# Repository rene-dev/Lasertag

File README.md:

# Lasertag
pew pew!
Ein freies und offenes Lasertag Projekt der warpzone in Münster.

## Aktueller Stand
Hard- und Software haben viele Kinderkrankheiten, spielbar ist es noch nicht. Es existieren 2 Waffel-Prototypen mit tiefgezogenen Gehäusen und ein Paar Hitpoints. Westen wollen noch gebaut werden.
* __Hitpoint__: voll funktionsfähig aber dirty gecoded
* __Lasermodul__: Im groben funktioniert alles. Einige Pins sind falsch beschriftet. IR funktioniert, sendet auch ganz leicht wenn es nicht senden soll. Sound ist viel zu leise.
* __Pi__: Da ist noch einiges zu tun. Grundlegende Kommunikation mit den Modulen ist möglich. Grundlegender Server Client per TCP.

## Grundstruktur
In jeder Waffel steckt ein Raspberry Pi, ein Lasermodul und ein Hitpoint. Das Lasermodul ist ein HAT für den Pi und dient als Schnittstelle zur Waffel-Hardware. Die High-Level Kommunikation (Spielmodus, Powerups, Map, ...) zwischen den Pis läuft per WLAN. Die Low-Level Kommunikation (Player-ID, Schaden) per gebündeltem IR-LED-UART auf TSOP-Empfänger.

### Raspberry Pi
In Python wird Netzwerk gemacht, per I2C die Module angesprochen und das SPI-Touch-Display angesteuert.

### Lasermodul
Kommt in jede Waffel:
* Atmega 328p
* IR-LED zum Daten senden
* roten Laser, damit man auch was sieht (Klasse 1 mit deutschem Zertifikat)
* starke RGBW ansteuern für Lichteffekte
* Trefferzone über einen Front-TSOP
* Taster auslesen
* LiPo auf 5V Step-Up Wandler
* An-Aus Taster
* Akkuüberwachung
* Audioverstärker

### Hitpoint
Kommt in jede Waffel und mehrere an die Weste (Schultern, Bauch, Rücken, ...):
* Attiny 2313A
* 4 10mm RGB-LEDs
* 4 TSOP-IR-Empfänger

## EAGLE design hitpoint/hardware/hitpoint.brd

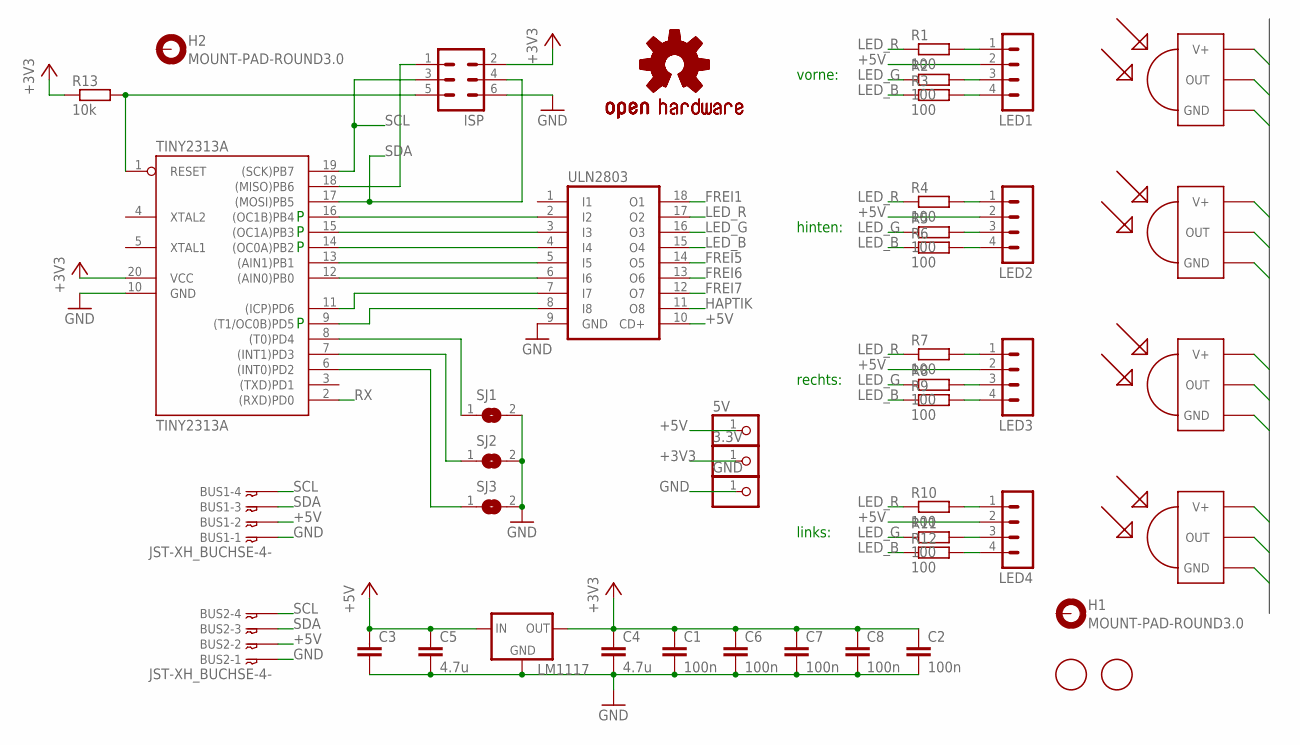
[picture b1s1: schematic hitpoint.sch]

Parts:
3.3V, 5V: PIN-HEADER-1
BUS1, BUS2: JST-XH_BUCHSE-4-; JST-XH_BUCHSE-4
C1, C2, C6, C7, C8: 100n; 0603
C3: C_EUCAP_UNIVERSAL; C_UNIVERSAL
C4, C5: 4.7u; 0805
GND: PIN-HEADER-1
H1, H2: MOUNT-PAD-ROUND3.0; 3,0-PAD
ISP: PIN-HEADER-3X2
LED1, LED2, LED3, LED4: PIN-HEADER-4
LM1117: LM1117_3V3_REGULATOR; SOT223
LOGO1, LOGO2: OSHW-LOGOM; OSHW-LOGO-M
R1, R2, R3, R4, R5, R6, R7, R8, R9, R10, R11, R12: 100; 0603
R13: 10k; 0603
SJ1, SJ2, SJ3: SJ
TINY2313A: TINY2313A; SO20LVERSTUMMELT
U$1, U$2, U$3, U$4: TSOP4338
U$5, U$6: FIDUCIAL; FIDUCIAL_1MM
ULN2803: ULN2803ASO18; SO18W

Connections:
+3V3: 3.3V.1, C1.1, C2.1, C4.1, C6.1, C7.1, C8.1, ISP.2, LM1117.2 (OUT), LM1117.4 (OUT), R13.1, TINY2313A.20 (VCC), U$1.VCC (V+), U$2.VCC (V+), U$3.VCC (V+), U$4.VCC (V+)
+5V: 5V.1, BUS1.P$2, BUS2.P$2, C3.1, C3.1B (1), C5.1, LED1.2, LED2.2, LED3.2, LED4.2, LM1117.3 (IN), ULN2803.10 (CD+)
FREI1: ULN2803.18 (O1)
FREI5: ULN2803.14 (O5)
FREI6: ULN2803.13 (O6)
FREI7: ULN2803.12 (O7)
GND: BUS1.P$1, BUS2.P$1, C1.2, C2.2, C3.2, C3.2B (2), C4.2, C5.2, C6.2, C7.2, C8.2, GND.1, ISP.6, LM1117.1 (GND), SJ1.2, SJ2.2, SJ3.2, TINY2313A.10 (GND), U$1.GND, U$2.GND, U$3.GND, U$4.GND, ULN2803.9 (GND)
HAPTIK: ULN2803.11 (O8)
LED_B: R3.1, R6.1, R9.1, R12.1, ULN2803.15 (O4)
LED_G: R2.1, R5.1, R8.1, R11.1, ULN2803.16 (O3)
LED_R: R1.1, R4.1, R7.1, R10.1, ULN2803.17 (O2)
unnamed: ISP.1, TINY2313A.18 ((MISO)PB6)
unnamed: SJ1.1, TINY2313A.8 ((T0)PD4)
unnamed: TINY2313A.16 ((OC1B)PB4), ULN2803.2 (I2)
unnamed: TINY2313A.15 ((OC1A)PB3), ULN2803.3 (I3)
unnamed: LED4.1, R10.2
unnamed: LED4.3, R11.2
unnamed: TINY2313A.14 ((OC0A)PB2), ULN2803.4 (I4)
unnamed: TINY2313A.13 ((AIN1)PB1), ULN2803.5 (I5)
unnamed: TINY2313A.12 ((AIN0)PB0), ULN2803.6 (I6)
unnamed: TINY2313A.11 ((ICP)PD6), ULN2803.7 (I7)
unnamed: TINY2313A.9 ((T1/OC0B)PD5), ULN2803.8 (I8)
unnamed: LED4.4, R12.2
unnamed: LED3.1, R7.2
unnamed: LED3.3, R8.2
unnamed: LED3.4, R9.2
unnamed: LED2.1, R4.2
unnamed: LED2.3, R5.2
unnamed: SJ2.1, TINY2313A.7 ((INT1)PD3)
unnamed: SJ3.1, TINY2313A.6 ((INT0)PD2)
unnamed: LED2.4, R6.2
unnamed: ISP.5, R13.2, TINY2313A.1 (RESET)
unnamed: LED1.1, R1.2
unnamed: LED1.3, R2.2
unnamed: LED1.4, R3.2
RX: TINY2313A.2 ((RXD)PD0), U$1.OUT, U$2.OUT, U$3.OUT, U$4.OUT
SCL: BUS1.P$4, BUS2.P$4, ISP.3, TINY2313A.19 ((SCK)PB7)
SDA: BUS1.P$3, BUS2.P$3, ISP.4, TINY2313A.17 ((MOSI)PB5)

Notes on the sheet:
vorne:
hinten:
rechts:
links:

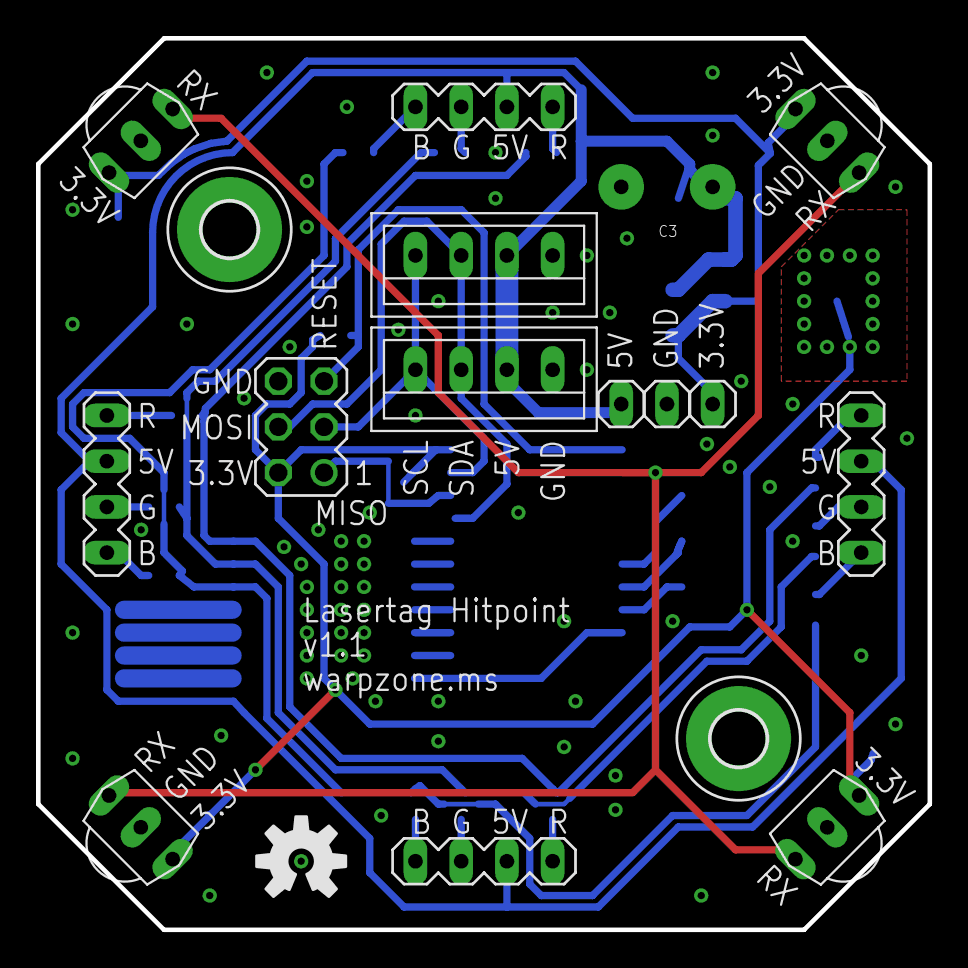
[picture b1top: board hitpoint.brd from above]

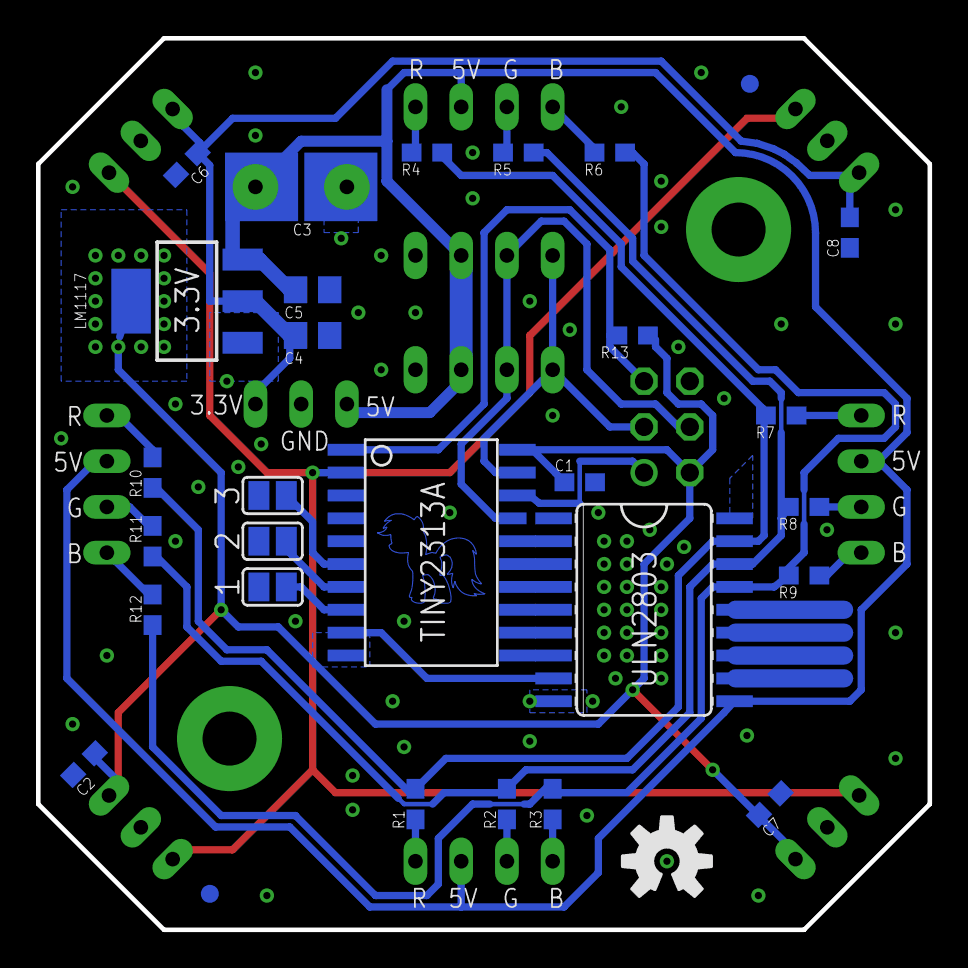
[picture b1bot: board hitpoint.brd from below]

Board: 2 copper layers, 49.5 x 49.5 mm, 47 parts (30 on the bottom side), 33 nets.

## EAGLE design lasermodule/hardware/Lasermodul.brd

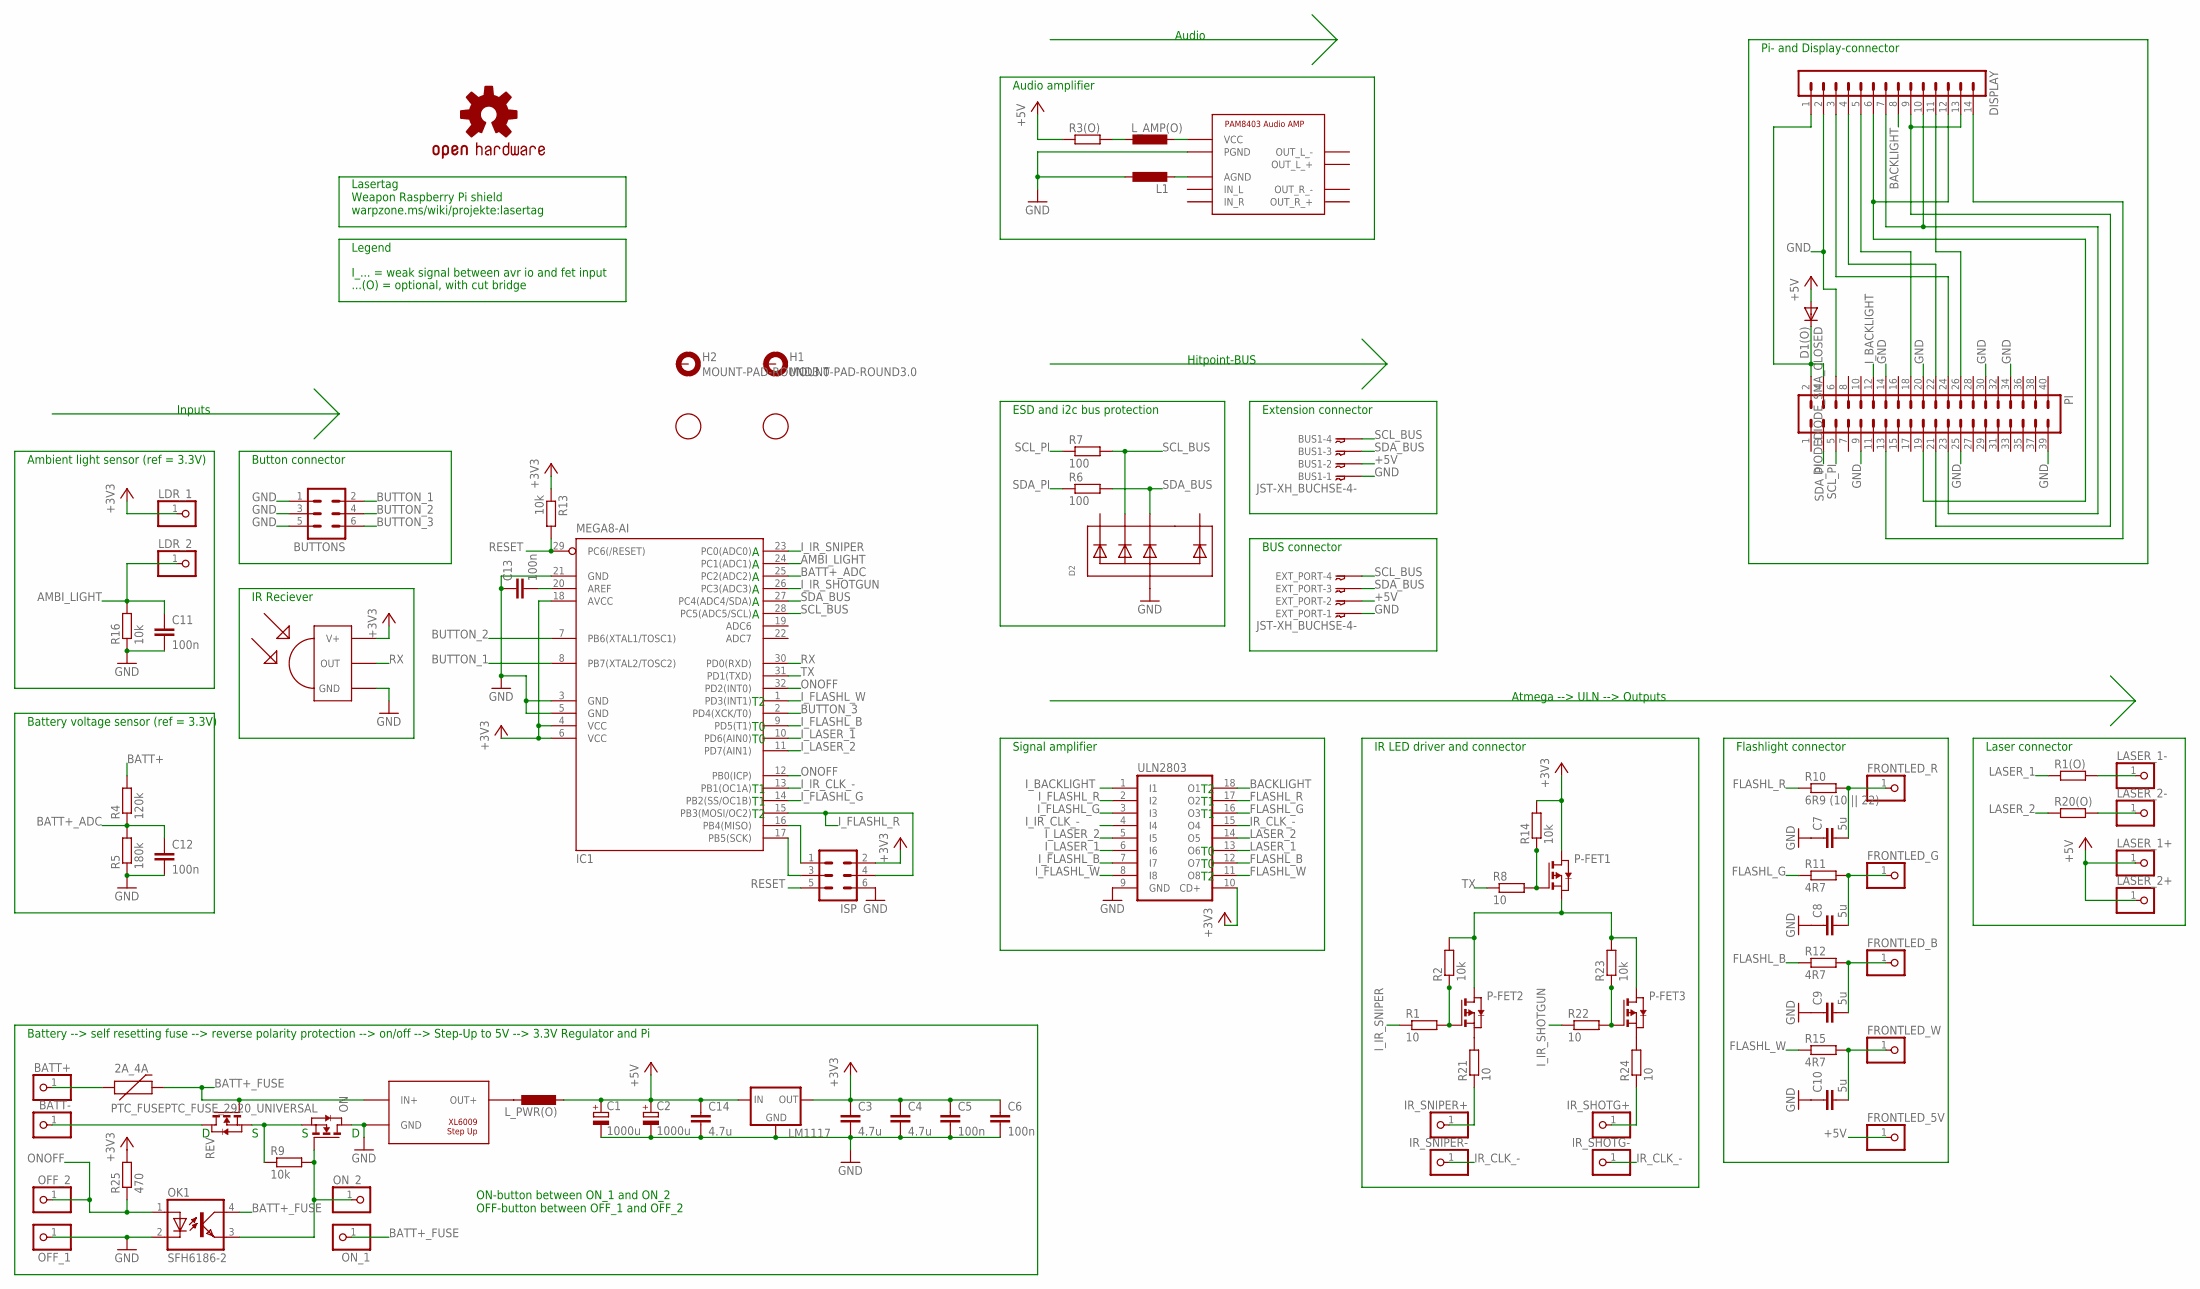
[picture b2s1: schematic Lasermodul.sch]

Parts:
2A_4A: PTC_FUSEPTC_FUSE_2920_UNIVERSAL; PTC_FUSE_2920_UNIVERSAL
BATT+: PIN-HEADER-1PIN-HEADER-1_BIG; PIN-HEADER-1_BIG
BATT-: PIN-HEADER-1PIN-HEADER-1_BIG; PIN-HEADER-1_BIG
BUS1: JST-XH_BUCHSE-4-; JST-XH_BUCHSE-4
BUTTONS: PIN-HEADER-3X2
C1, C2: 1000u; C_UNIVERSAL_PAD
C3, C4, C14: 4.7u; 0805
C5, C6, C11, C12, C13: 100n; 0603
C7, C8, C9, C10: 5u; 0805
D1(O): DIODEDIODE_SMA_CLOSED; DIODE_SMA_CLOSED
D2: ESD-SCHUTZ; SOT363
DISPLAY: PIN-HEADER-DISPLAY
EXT_PORT: JST-XH_BUCHSE-4-; JST-XH_BUCHSE-4
FRONTLED_5V: PIN-HEADER-1PIN-HEADER-1; PIN-HEADER-1
FRONTLED_B: PIN-HEADER-1PIN-HEADER-1; PIN-HEADER-1
FRONTLED_G: PIN-HEADER-1PIN-HEADER-1; PIN-HEADER-1
FRONTLED_R: PIN-HEADER-1PIN-HEADER-1; PIN-HEADER-1
FRONTLED_W: PIN-HEADER-1PIN-HEADER-1; PIN-HEADER-1
H1, H2: MOUNT-PAD-ROUND3.0; 3,0-PAD
IC1: MEGA8-AI; TQFP32-08
IR_SHOTG+: PIN-HEADER-1PIN-HEADER-1; PIN-HEADER-1
IR_SHOTG-: PIN-HEADER-1PIN-HEADER-1; PIN-HEADER-1
IR_SNIPER+: PIN-HEADER-1PIN-HEADER-1; PIN-HEADER-1
IR_SNIPER-: PIN-HEADER-1PIN-HEADER-1; PIN-HEADER-1
ISP: PIN-HEADER-3X2
L1: L-EUL2825P; L2825P
LASER_1+, LASER_1-, LASER_2+, LASER_2-: PIN-HEADER-1PIN-HEADER-1; PIN-HEADER-1
LDR_1, LDR_2: PIN-HEADER-1PIN-HEADER-1; PIN-HEADER-1
LM1117: LM1117_3V3_REGULATOR; SOT223
LOGO1: OSHW-LOGOM; OSHW-LOGO-M
L_AMP(O): L; L_5MM_CLOSED
L_PWR(O): L; L_5MM_CLOSED
OFF_1, OFF_2: PIN-HEADER-1PIN-HEADER-1; PIN-HEADER-1
OK1: SFH6186-2; SMD4-7
ON: N-MOSFET; TO252
ON_1, ON_2: PIN-HEADER-1PIN-HEADER-1; PIN-HEADER-1
P-FET1, P-FET2, P-FET3: PMOSSOT23; SOT-23
PI: PIN-HEADER-20X2
R1, R8, R21, R22, R24: 10; 0603
R1(O), R20(O): R_EU0603_CLOSED; 0603_CLOSED
R2, R9, R13, R14, R16, R23: 10k; 0603
R3(O): R_EU0805_CLOSED; 0805_CLOSED
R4: 120k; 0603
R5: 180k; 0603
R6, R7: 100; 0603
R10: 6R9 (10 || 22); 0603
R11, R12, R15: 4R7; 0603
R25: 470; 0603
REV: N-MOSFET; TO252
U$1: TSOP1838; TSOP18XX
U$3: XL6009-STEPUP-BOARD
U$4: PAM8403-AMP-BOARD
U$5, U$6: FIDUCIAL; FIDUCIAL_1MM
ULN2803: ULN2803ASO18; SO18W

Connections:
+3V3: C3.1, C4.1, C5.1, C6.1, IC1.4 (VCC), IC1.6 (VCC), IC1.18 (AVCC), ISP.2, LDR_1.1, LM1117.2 (OUT), LM1117.4 (OUT), P-FET1.1 (D), R13.1, R14.2, R25.2, U$1.VCC (V+), ULN2803.10 (CD+)
+5V: BUS1.P$2, C1.+, C2.+, C14.1, D1(O).A, EXT_PORT.P$2, FRONTLED_5V.1, LASER_1+.1, LASER_2+.1, LM1117.3 (IN), L_PWR(O).2, R3(O).1
AMBI_LIGHT: C11.1, IC1.24 (PC1(ADC1)), LDR_2.1, R16.2
BACKLIGHT: DISPLAY.8, ULN2803.18 (O1)
BATT+: 2A_4A.P$1 (1), BATT+.1, R4.2
BATT+_ADC: C12.1, IC1.25 (PC2(ADC2)), R4.1, R5.2
BATT+_FUSE: 2A_4A.P$2 (2), OK1.4 (COL), ON_1.1, REV.1 (G), U$3.IN+
BATT-: BATT-.1, REV.3 (D)
BUTTON_1: BUTTONS.2, IC1.8 (PB7(XTAL2/TOSC2))
BUTTON_2: BUTTONS.4, IC1.7 (PB6(XTAL1/TOSC1))
BUTTON_3: BUTTONS.6, IC1.2 (PD4(XCK/T0))
EASTEREGG_NET: P-FET1.2 (S), P-FET2.1 (D), P-FET3.1 (D), R2.2, R23.2
FLASHL_B: R12.1, ULN2803.12 (O7)
FLASHL_G: R11.1, ULN2803.16 (O3)
FLASHL_R: R10.1, ULN2803.17 (O2)
FLASHL_W: R15.1, ULN2803.11 (O8)
GND: BUS1.P$1, BUTTONS.1, BUTTONS.3, BUTTONS.5, C1.-, C2.-, C3.2, C4.2, C5.2, C6.2, C7.1, C8.1, C9.1, C10.1, C11.2, C12.2, C13.1, C14.2, D2.2 (A), DISPLAY.2, EXT_PORT.P$1, IC1.3 (GND), IC1.5 (GND), IC1.21 (GND), ISP.6, L1.1, LM1117.1 (GND), OFF_1.1, OK1.2 (C), ON.3 (D), PI.6, PI.9, PI.14, PI.20, PI.25, PI.30, PI.34, PI.39, R5.1, R16.1, U$1.GND, U$3.GND_IN (GND), U$3.GND_OUT (GND), U$4.PGND, ULN2803.9 (GND)
IR_CLK_-: IR_SHOTG-.1, IR_SNIPER-.1, ULN2803.15 (O4)
IR_SHOTGUN_TX_+: IR_SHOTG+.1, R24.1
IR_SNIPER_TX_+: IR_SNIPER+.1, R21.1
I_BACKLIGHT: PI.12, ULN2803.1 (I1)
I_FLASHL_B: IC1.9 (PD5(T1)), ULN2803.7 (I7)
I_FLASHL_G: IC1.14 (PB2(SS/OC1B)), ULN2803.3 (I3)
I_FLASHL_R: IC1.15 (PB3(MOSI/OC2)), ISP.4, ULN2803.2 (I2)
I_FLASHL_W: IC1.1 (PD3(INT1)), ULN2803.8 (I8)
I_IR_CLK_-: IC1.13 (PB1(OC1A)), ULN2803.4 (I4)
I_IR_SHOTGUN: IC1.26 (PC3(ADC3)), R22.1
I_IR_SNIPER: IC1.23 (PC0(ADC0)), R1.1
I_LASER_1: IC1.10 (PD6(AIN0)), ULN2803.6 (I6)
I_LASER_2: IC1.11 (PD7(AIN1)), ULN2803.5 (I5)
LASER_1: R1(O).1, ULN2803.13 (O6)
LASER_1-: LASER_1-.1, R1(O).2
LASER_2: R20(O).1, ULN2803.14 (O5)
LASER_2-: LASER_2-.1, R20(O).2
LCD_CS: DISPLAY.3, PI.24
LCD_DC: DISPLAY.5, PI.18
LCD_MISO: DISPLAY.9, DISPLAY.13, PI.21
LCD_MOSI: DISPLAY.6, DISPLAY.12, PI.19
LCD_RESET: DISPLAY.4, PI.22
LCD_SCK: DISPLAY.7, DISPLAY.10, PI.23
LCD_TOUCH_CS: DISPLAY.11, PI.26
LCD_TOUCH_IRQ: DISPLAY.14, PI.13
unnamed: L1.2, U$4.AGND
unnamed: IC1.16 (PB4(MISO)), ISP.1
unnamed: IC1.17 (PB5(SCK)), ISP.3
unnamed: C7.2, FRONTLED_R.1, R10.2
unnamed: P-FET1.3 (G), R8.2, R14.1
unnamed: C13.2, IC1.20 (AREF)
unnamed: P-FET2.3 (G), R1.2, R2.1
unnamed: C8.2, FRONTLED_G.1, R11.2
unnamed: C9.2, FRONTLED_B.1, R12.2
unnamed: C10.2, FRONTLED_W.1, R15.2
unnamed: L_PWR(O).1, U$3.OUT+
unnamed: ON.2 (S), R9.1, REV.2 (S)
unnamed: P-FET2.2 (S), R21.2
unnamed: D1(O).C, DISPLAY.1, PI.2, PI.4
unnamed: L_AMP(O).2, R3(O).2
unnamed: L_AMP(O).1, U$4.VCC
unnamed: P-FET3.2 (S), R24.2
unnamed: P-FET3.3 (G), R22.2, R23.1
ONOFF: IC1.12 (PB0(ICP)), IC1.32 (PD2(INT0)), OFF_2.1, OK1.1 (A), R25.1
ONOFF_2: OK1.3 (EMIT), ON.1 (G), ON_2.1, R9.2
RESET: IC1.29 (PC6(/RESET)), ISP.5, R13.2
RX: IC1.30 (PD0(RXD)), U$1.OUT
SCL_BUS: BUS1.P$4, D2.3 (C2), EXT_PORT.P$4, IC1.28 (PC5(ADC5/SCL)), R7.2
SCL_PI: PI.5, R7.1
SDA_BUS: BUS1.P$3, D2.4 (C3), EXT_PORT.P$3, IC1.27 (PC4(ADC4/SDA)), R6.2
SDA_PI: PI.3, R6.1
TX: IC1.31 (PD1(TXD)), R8.1

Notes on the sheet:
Flashlight connector
Laser connector
BUS connector
ESD and i2c bus protection
IR Reciever
Audio amplifier
Battery --> self resetting fuse --> reverse polarity protection --> on/off --> Step-Up to 5V --> 3.3V Regulator and Pi
Pi- and Display-connector
Battery voltage sensor (ref = 3.3V)
Ambient light sensor (ref = 3.3V)
IR LED driver and connector
Signal amplifier
Button connector
Extension connector
I_... = weak signal between avr io and fet input
Legend
...(O) = optional, with cut bridge
Hitpoint-BUS
ON-button between ON_1 and ON_2 OFF-button between OFF_1 and OFF_2
Atmega --> ULN --> Outputs
Inputs
Audio
Lasertag Weapon Raspberry Pi shield warpzone.ms/wiki/projekte:lasertag

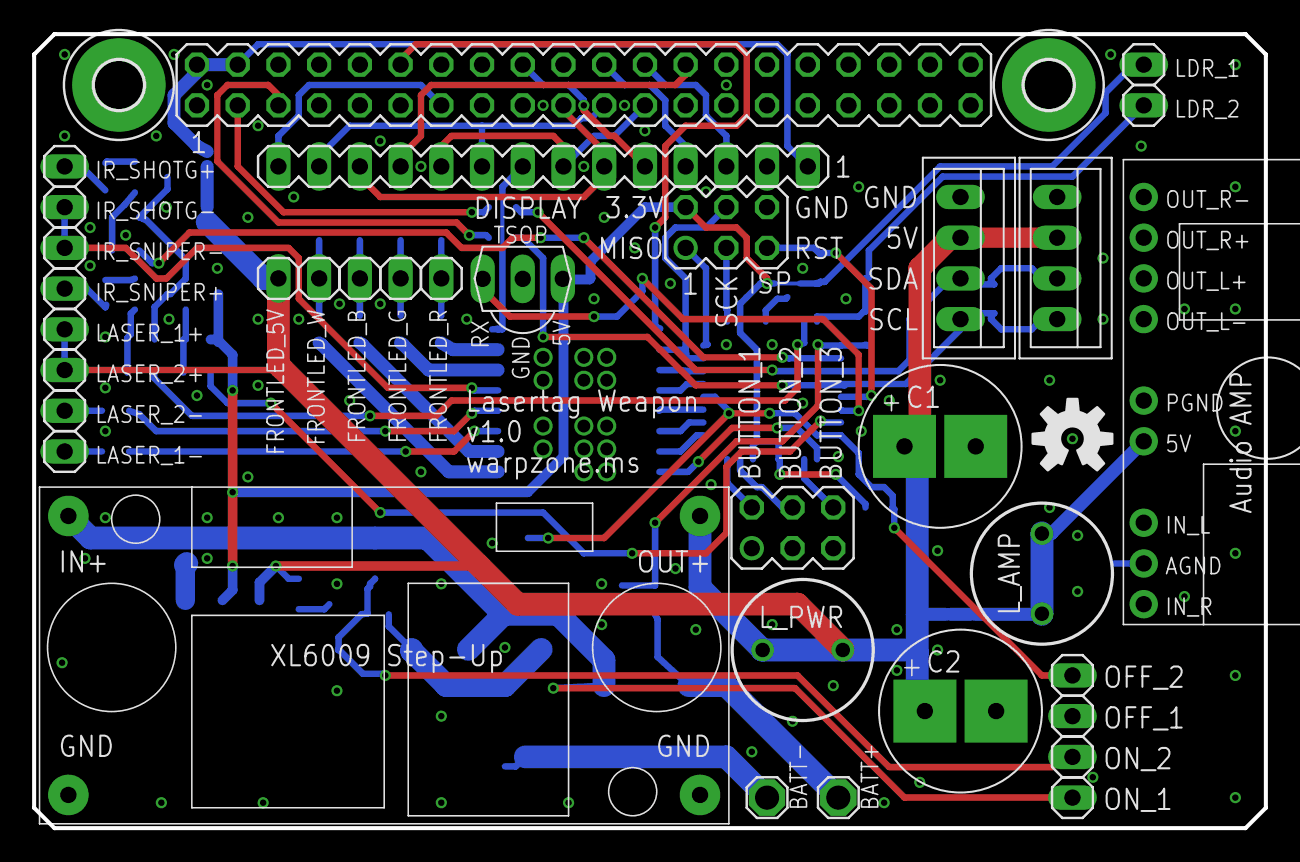
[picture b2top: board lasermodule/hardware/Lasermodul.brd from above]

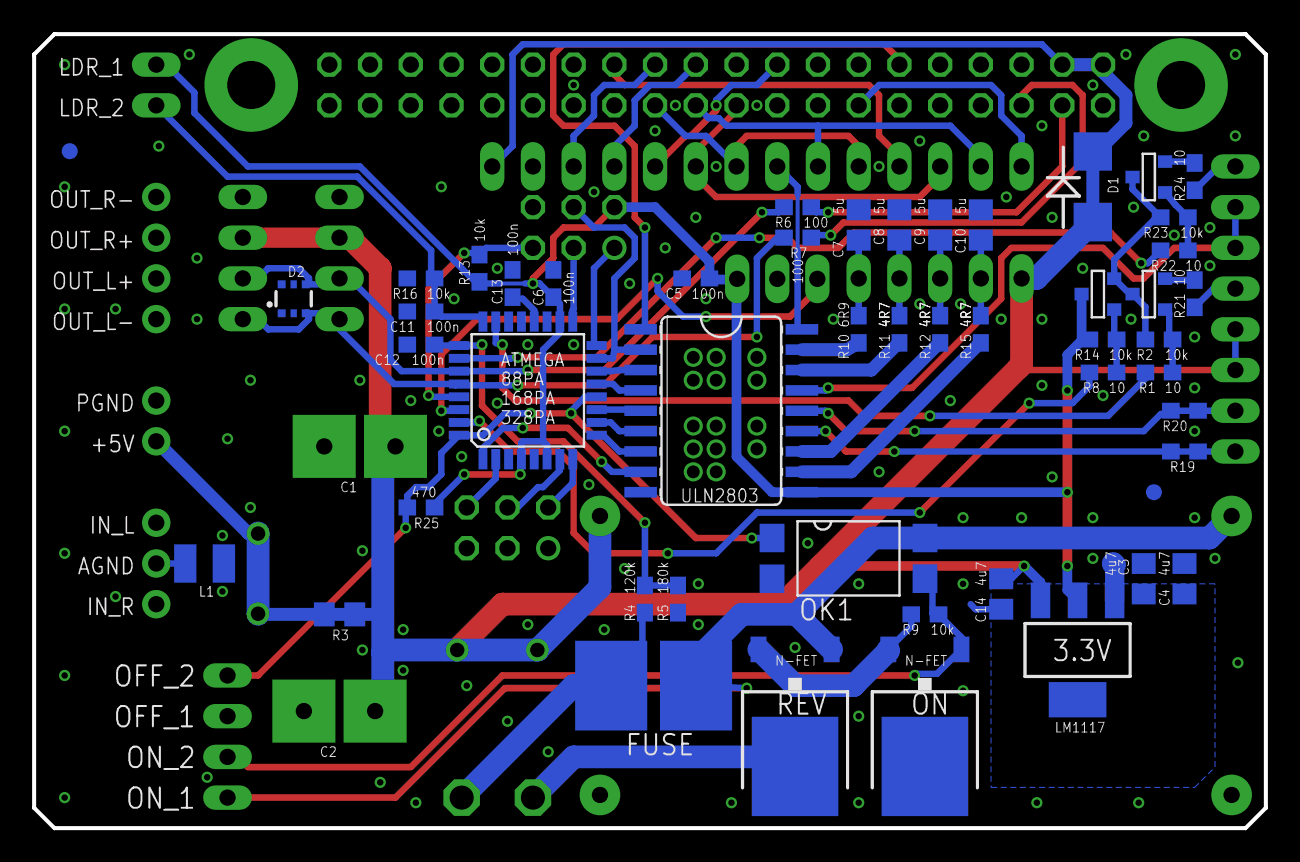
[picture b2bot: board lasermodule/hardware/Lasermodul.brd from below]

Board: 2 copper layers, 76.8 x 49.5 mm, 88 parts (50 on the bottom side), 69 nets.

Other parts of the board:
U$2: PI2

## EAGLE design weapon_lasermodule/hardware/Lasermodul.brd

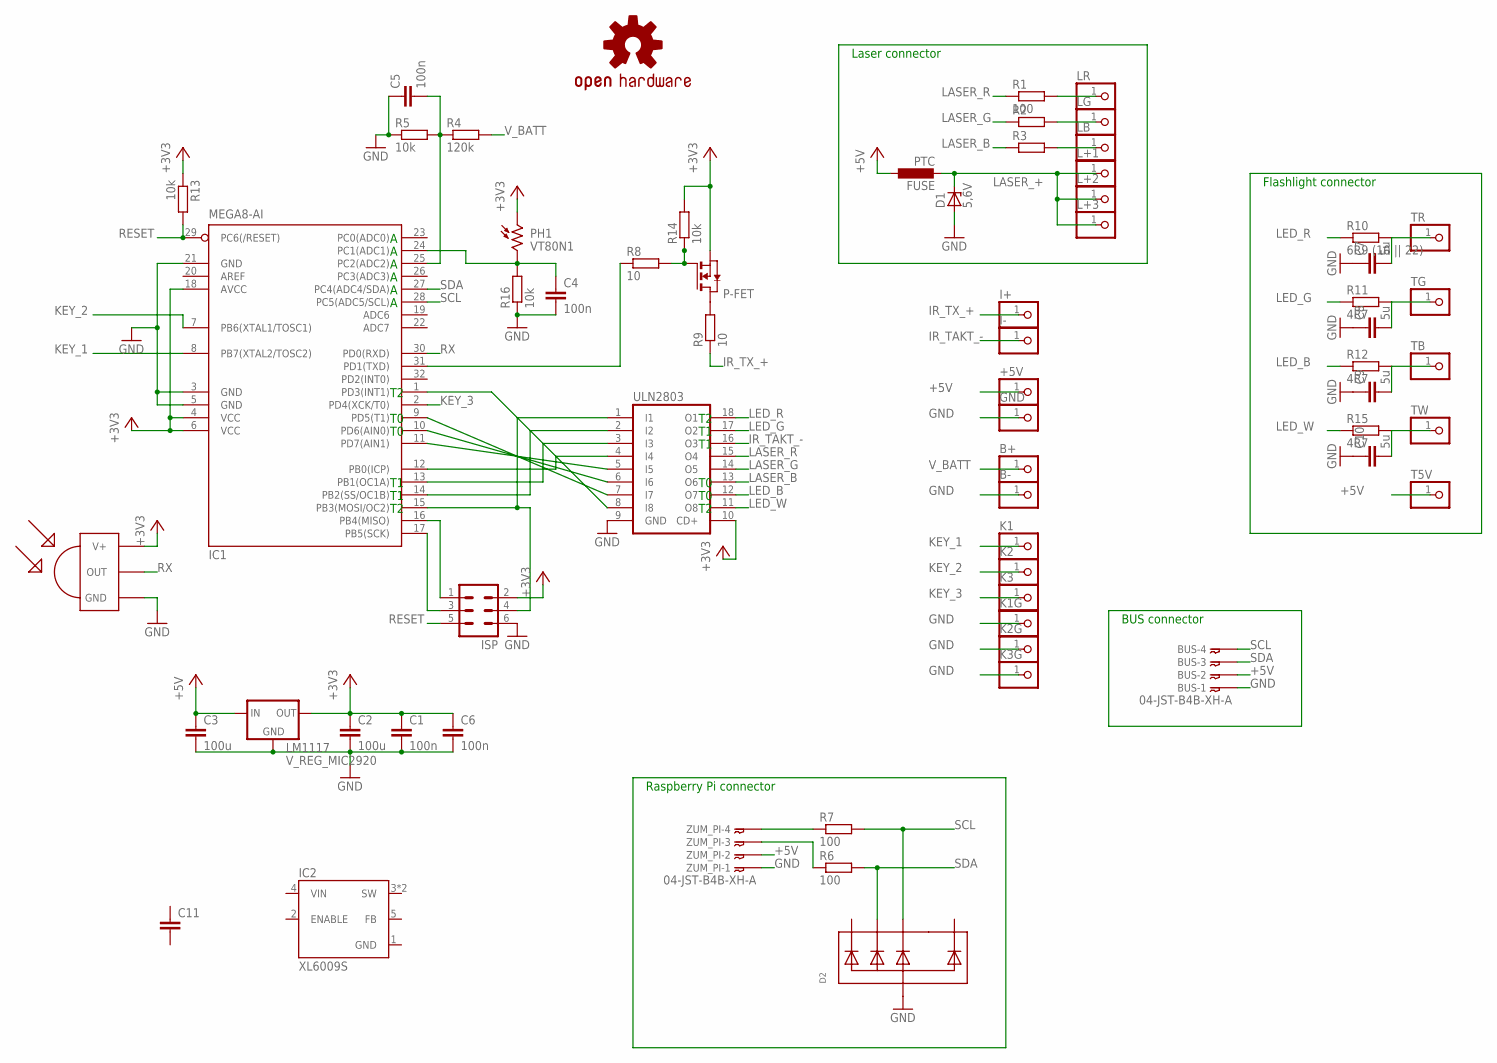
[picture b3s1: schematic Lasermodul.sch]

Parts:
+5V: PINHD-1X1; 1X01
B+: PINHD-1X1; 1X01
B-: PINHD-1X1; 1X01
BUS: 04-JST-B4B-XH-A; B4B-XH
C1, C4, C5, C6: 100n; C0805
C2, C3: 100u; C1808
C7, C8, C9, C10: 5u; C0805
C11: C_EUCAP_UNIVERSAL; C_UNIVERSAL
D1: 5,6V; F126Z12
D2: TVSARRAY_5LANE; SOT363
FUSE: PTC; L1812
GND: PINHD-1X1; 1X01
I+: PINHD-1X1; 1X01
I-: PINHD-1X1; 1X01
IC1: MEGA8-AI; TQFP32-08
IC2: XL6009S; TO263-5
ISP: MA03-2
K1, K1G, K2, K2G, K3, K3G: PINHD-1X1; 1X01
L+1, L+2, L+3: PINHD-1X1; 1X01
LB: PINHD-1X1; 1X01
LG: PINHD-1X1; 1X01
LM1117: V_REG_MIC2920; SOT223
LOGO1: OSHW-LOGOM; OSHW-LOGO-M
LR: PINHD-1X1; 1X01
P-FET: NMOSSOT23; SOT-23
PH1: VT80N1; VT800
R1, R6, R7: 100; R0805
R2, R3: R-EU_R0805; R0805
R4: 120k; R0805
R5, R13, R14, R16: 10k; R0805
R8, R9: 10; R0805
R10: 6R9 (10 || 22); R0805
R11, R12, R15: 4R7; R0805
T5V: PINHD-1X1; 1X01
TB: PINHD-1X1; 1X01
TG: PINHD-1X1; 1X01
TR: PINHD-1X1; 1X01
TW: PINHD-1X1; 1X01
U$1: TSOP1838; TSOP18XX
ULN2803: ULN2803ASO18; SO18W
ZUM_PI: 04-JST-B4B-XH-A; B4B-XH

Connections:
+3V3: C1.1, C2.1, C6.1, IC1.4 (VCC), IC1.6 (VCC), IC1.18 (AVCC), ISP.2, LM1117.2 (OUT), LM1117.4 (OUT), P-FET.2 (S), PH1.1, R13.1, R14.2, U$1.VCC (V+), ULN2803.10 (CD+)
+5V: +5V.1, BUS.P$2, C3.1, FUSE.1, LM1117.3 (IN), T5V.1, ZUM_PI.P$2
GND: B-.1, BUS.P$1, C1.2, C2.2, C3.2, C4.2, C5.1, C6.2, C7.1, C8.1, C9.1, C10.1, D1.A, D2.2 (A), GND.1, IC1.3 (GND), IC1.5 (GND), IC1.21 (GND), IC2.1 (GND), ISP.6, K1G.1, K2G.1, K3G.1, LM1117.1 (GND), R5.1, R16.1, U$1.GND, ULN2803.9 (GND), ZUM_PI.P$1
IR_TAKT_-: I-.1, ULN2803.16 (O3)
IR_TX_+: I+.1, R9.1
KEY_1: IC1.8 (PB7(XTAL2/TOSC2)), K1.1
KEY_2: IC1.7 (PB6(XTAL1/TOSC1)), K2.1
KEY_3: IC1.2 (PD4(XCK/T0)), K3.1
LASER_+: D1.C, FUSE.2, L+1.1, L+2.1, L+3.1
LASER_B: R3.1, ULN2803.13 (O6)
LASER_G: R2.1, ULN2803.14 (O5)
LASER_R: R1.1, ULN2803.15 (O4)
LED_B: R12.1, ULN2803.12 (O7)
LED_G: R11.1, ULN2803.17 (O2)
LED_R: R10.1, ULN2803.18 (O1)
LED_W: R15.1, ULN2803.11 (O8)
unnamed: IC1.15 (PB3(MOSI/OC2)), ISP.4, ULN2803.1 (I1)
unnamed: IC1.14 (PB2(SS/OC1B)), ULN2803.2 (I2)
unnamed: IC1.13 (PB1(OC1A)), ULN2803.3 (I3)
unnamed: IC1.12 (PB0(ICP)), ULN2803.4 (I4)
unnamed: IC1.11 (PD7(AIN1)), ULN2803.5 (I5)
unnamed: IC1.1 (PD3(INT1)), ULN2803.8 (I8)
unnamed: IC1.10 (PD6(AIN0)), ULN2803.6 (I6)
unnamed: IC1.9 (PD5(T1)), ULN2803.7 (I7)
unnamed: IC1.16 (PB4(MISO)), ISP.1
unnamed: LR.1, R1.2
unnamed: IC1.17 (PB5(SCK)), ISP.3
unnamed: C5.2, IC1.25 (PC2(ADC2)), R4.1, R5.2
unnamed: C7.2, R10.2, TR.1
unnamed: P-FET.1 (D), R9.2
unnamed: IC1.31 (PD1(TXD)), R8.1
unnamed: LG.1, R2.2
unnamed: LB.1, R3.2
unnamed: P-FET.3 (G), R8.2, R14.1
unnamed: C8.2, R11.2, TG.1
unnamed: C9.2, R12.2, TB.1
unnamed: C10.2, R15.2, TW.1
unnamed: C4.1, IC1.24 (PC1(ADC1)), PH1.2, R16.2
unnamed: R7.1, ZUM_PI.P$4
unnamed: R6.1, ZUM_PI.P$3
RESET: IC1.29 (PC6(/RESET)), ISP.5, R13.2
RX: IC1.30 (PD0(RXD)), U$1.OUT
SCL: BUS.P$4, D2.4 (C3), IC1.28 (PC5(ADC5/SCL)), R7.2
SDA: BUS.P$3, D2.3 (C2), IC1.27 (PC4(ADC4/SDA)), R6.2
VIN: IC2.4 (VIN)
V_BATT: B+.1, R4.2

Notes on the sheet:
Flashlight connector
Laser connector
BUS connector
Raspberry Pi connector

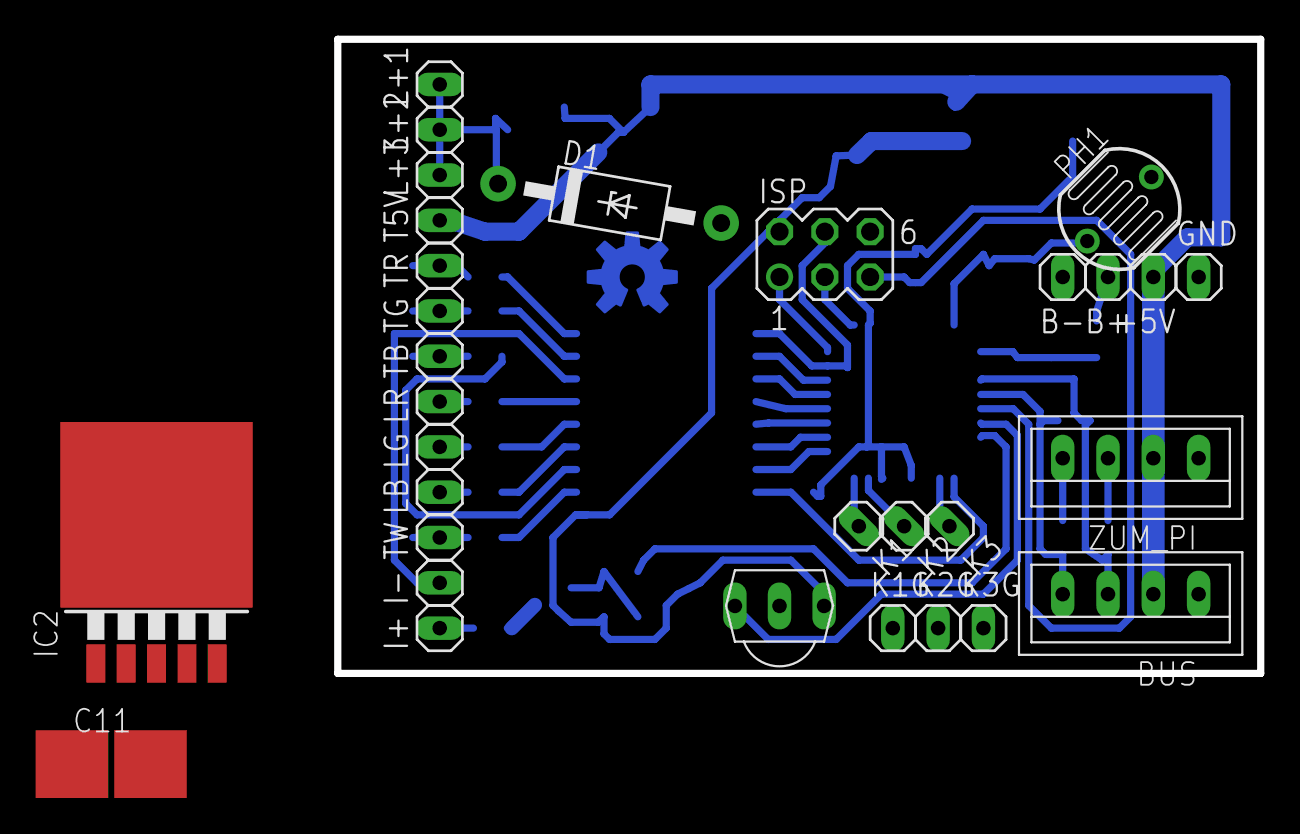
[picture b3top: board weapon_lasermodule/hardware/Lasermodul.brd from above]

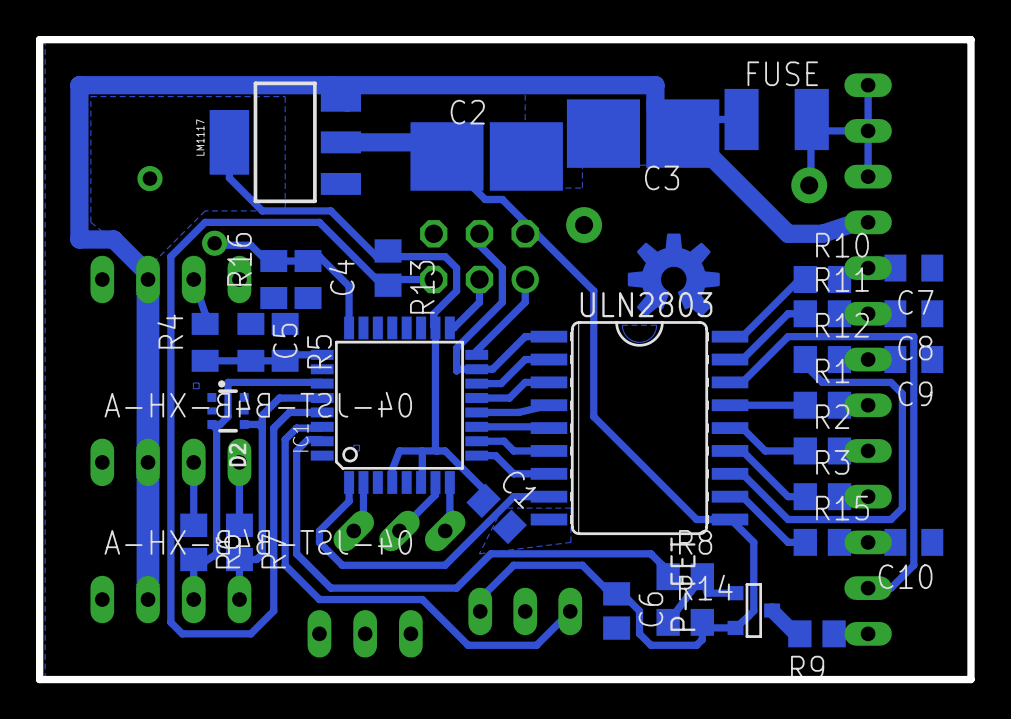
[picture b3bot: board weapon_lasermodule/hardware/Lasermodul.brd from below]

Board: 2 copper layers, 51.7 x 35.5 mm, 64 parts (32 on the bottom side), 45 nets.

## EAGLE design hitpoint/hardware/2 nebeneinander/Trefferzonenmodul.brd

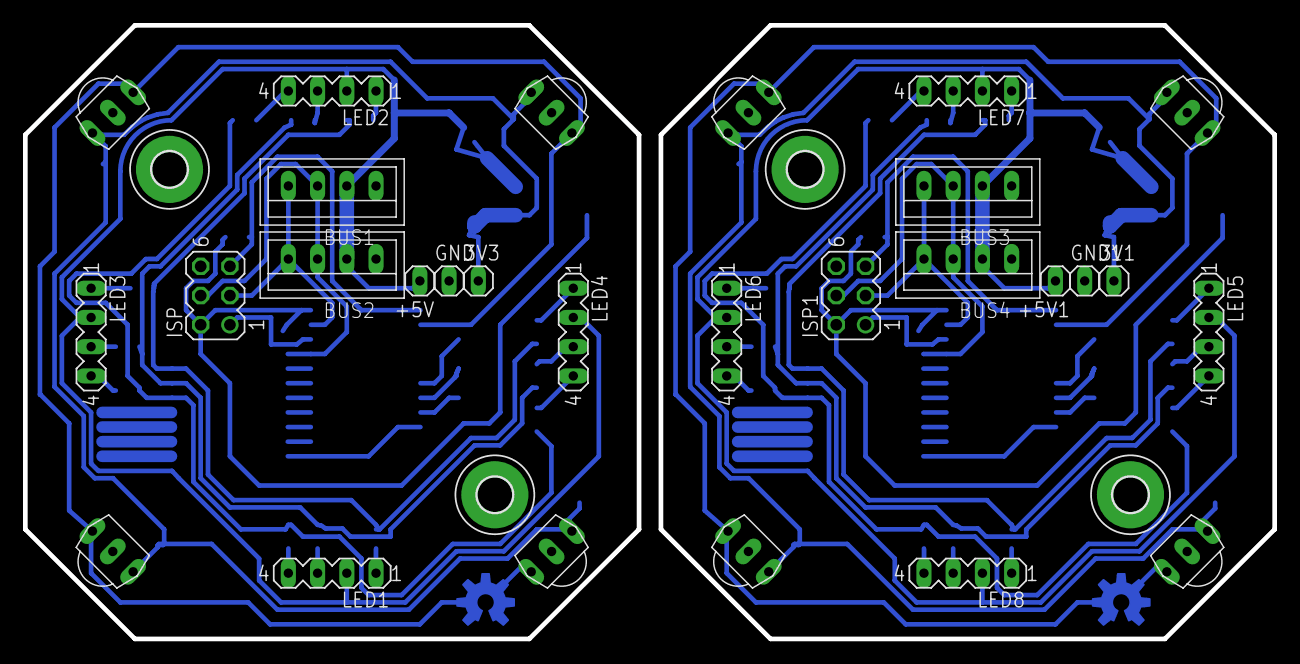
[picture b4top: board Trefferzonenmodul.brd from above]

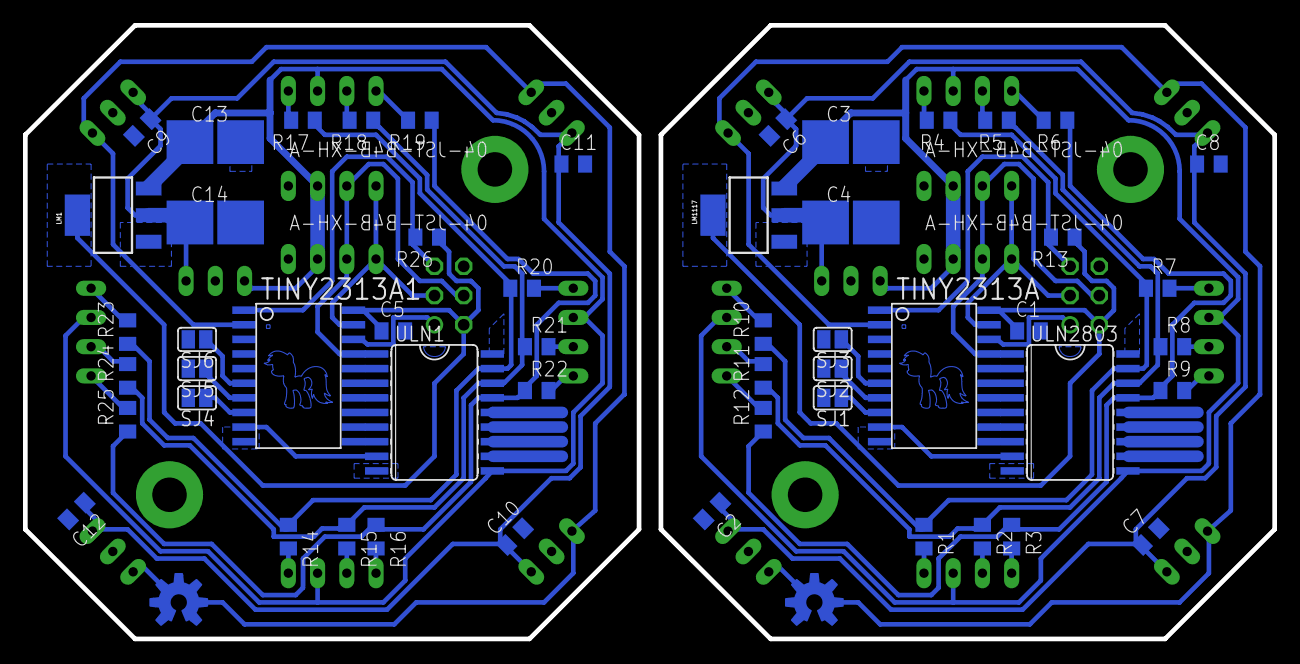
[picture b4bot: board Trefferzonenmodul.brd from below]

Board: 2 copper layers, 108.6 x 53.3 mm, 86 parts (52 on the bottom side), 66 nets.

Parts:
3V1, 3V3: 1X01
+5V, +5V1: 1X01
BUS1, BUS2, BUS3, BUS4: 04-JST-B4B-XH-A; B4B-XH
C1, C2, C5, C6, C7, C8, C9, C10, C11, C12: 100n; C0805
C3, C4, C13, C14: C1808
GND, GND1: 1X01
H1, H2, H3, H4: MOUNT-PAD-ROUND3.0; 3,0-PAD
ISP, ISP1: MA03-2
LED1, LED2, LED3, LED4, LED5, LED6, LED7, LED8: MA04-1
LM1, LM1117: V_REG_MIC2920; SOT223
LOGO1, LOGO2: OSHW-LOGOM; OSHW-LOGO-M
R1, R2, R3, R4, R5, R6, R7, R8, R9, R10, R11, R12, R14, R15, R16, R17, R18, R19, R20, R21, R22, R23, R24, R25: 100; R0805
R13, R26: 10k; R0805
SJ1, SJ2, SJ3, SJ4, SJ5, SJ6: SJ
TINY2313A, TINY2313A1: AT90S2313S; SO20L
U$1, U$2, U$3, U$4, U$5, U$6, U$7, U$8: TSOP1838; TSOP18XX
ULN1, ULN2803: SO18W

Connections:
+3V1: 3V1.1, C5.1, C9.1, C10.1, C11.1, C12.1, C14.1, ISP1.2, LM1.2, LM1.4, R26.1, TINY2313A1.20, U$5.VCC, U$6.VCC, U$7.VCC, U$8.VCC
+3V3: 3V3.1, C1.1, C2.1, C4.1, C6.1, C7.1, C8.1, ISP.2, LM1117.2, LM1117.4, R13.1, TINY2313A.20, U$1.VCC, U$2.VCC, U$3.VCC, U$4.VCC
+5V: +5V.1, BUS1.P$2, BUS2.P$2, C3.1, LED1.2, LED2.2, LED3.2, LED4.2, LM1117.3, ULN2803.10
+5V1: +5V1.1, BUS3.P$2, BUS4.P$2, C13.1, LED5.2, LED6.2, LED7.2, LED8.2, LM1.3, ULN1.10
GND: BUS1.P$1, BUS2.P$1, C1.2, C2.2, C3.2, C4.2, C6.2, C7.2, C8.2, GND.1, ISP.6, LM1117.1, SJ1.2, SJ2.2, SJ3.2, TINY2313A.10, U$1.GND, U$2.GND, U$3.GND, U$4.GND, ULN2803.9
GND1: BUS3.P$1, BUS4.P$1, C5.2, C9.2, C10.2, C11.2, C12.2, C13.2, C14.2, GND1.1, ISP1.6, LM1.1, SJ4.2, SJ5.2, SJ6.2, TINY2313A1.10, U$5.GND, U$6.GND, U$7.GND, U$8.GND, ULN1.9
LED_B: R3.1, R6.1, R9.1, R12.1, ULN2803.15
LED_B1: R16.1, R19.1, R22.1, R25.1, ULN1.15
LED_G: R2.1, R5.1, R8.1, R11.1, ULN2803.16
LED_G1: R15.1, R18.1, R21.1, R24.1, ULN1.16
LED_R: R1.1, R4.1, R7.1, R10.1, ULN2803.17
LED_R1: R14.1, R17.1, R20.1, R23.1, ULN1.17
unnamed: ISP.1, TINY2313A.18
unnamed: SJ1.1, TINY2313A.8
unnamed: TINY2313A.16, ULN2803.2
unnamed: TINY2313A.15, ULN2803.3
unnamed: LED4.1, R10.2
unnamed: LED4.3, R11.2
unnamed: TINY2313A.14, ULN2803.4
unnamed: TINY2313A.13, ULN2803.5
unnamed: TINY2313A.12, ULN2803.6
unnamed: TINY2313A.11, ULN2803.7
unnamed: TINY2313A.9, ULN2803.8
unnamed: LED4.4, R12.2
unnamed: LED3.1, R7.2
unnamed: LED3.3, R8.2
unnamed: LED3.4, R9.2
unnamed: LED2.1, R4.2
unnamed: LED2.3, R5.2
unnamed: SJ2.1, TINY2313A.7
unnamed: SJ3.1, TINY2313A.6
unnamed: LED2.4, R6.2
unnamed: ISP.5, R13.2, TINY2313A.1
unnamed: LED1.1, R1.2
unnamed: LED1.3, R2.2
unnamed: LED1.4, R3.2
unnamed: ISP1.1, TINY2313A1.18
unnamed: TINY2313A1.16, ULN1.2
unnamed: TINY2313A1.15, ULN1.3
unnamed: TINY2313A1.14, ULN1.4
unnamed: TINY2313A1.13, ULN1.5
unnamed: TINY2313A1.12, ULN1.6
unnamed: TINY2313A1.11, ULN1.7
unnamed: TINY2313A1.9, ULN1.8
unnamed: SJ4.1, TINY2313A1.8
unnamed: SJ5.1, TINY2313A1.7
unnamed: SJ6.1, TINY2313A1.6
unnamed: ISP1.5, R26.2, TINY2313A1.1
unnamed: LED5.1, R23.2
unnamed: LED5.3, R24.2
unnamed: LED5.4, R25.2
unnamed: LED6.1, R20.2
unnamed: LED6.3, R21.2
unnamed: LED6.4, R22.2
unnamed: LED7.1, R17.2
unnamed: LED7.3, R18.2
unnamed: LED7.4, R19.2
unnamed: LED8.1, R14.2
unnamed: LED8.3, R15.2
unnamed: LED8.4, R16.2
RX: TINY2313A.2, U$1.OUT, U$2.OUT, U$3.OUT, U$4.OUT
RX1: TINY2313A1.2, U$5.OUT, U$6.OUT, U$7.OUT, U$8.OUT
SCL: BUS1.P$4, BUS2.P$4, ISP.3, TINY2313A.19
SCL1: BUS3.P$4, BUS4.P$4, ISP1.3, TINY2313A1.19
SDA: BUS1.P$3, BUS2.P$3, ISP.4, TINY2313A.17, ULN2803.1
SDA1: BUS3.P$3, BUS4.P$3, ISP1.4, TINY2313A1.17, ULN1.1

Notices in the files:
parts and their libraries:
SparkFun-Aesthetics: Licensing: Creative Commons ShareAlike 4.0 International - https://creativecommons.org/licenses/by-sa/4.0
